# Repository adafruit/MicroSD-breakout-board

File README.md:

## Adafruit MicroSD breakout board PCB
<a href="http://www.adafruit.com/products/254"><br/>
Click here to purchase one from the Adafruit shop</a>

Not just a simple breakout board, this microSD adapter goes the extra mile - designed for ease of use.

- Onboard 5v->3v regulator provides 150mA for power-hungry cards
- 3v level shifting means you can use this with ease on either 3v or 5v systems
- Uses a proper level shifting chip, not resistors: less problems, and faster read/write access
- Use 3 or 4 digital pins to read and write 2Gb+ of storage!
- Activity LED lights up when the SD card is being read or written
- Four #2 mounting holes
- Push-push socket with card slightly over the edge of the PCB so its easy to insert and remove
- Comes with 0.1" header (unattached) so you can get it on a breadboard or use wires - your choice
- Tested and assembled here at the Adafruit factory
- Works great with Arduino, with tons of example code and wiring diagrams

This repo contains the PCB files for the Adafruit SPI Micro SD (transflash) breakout board

### License

Adafruit invests time and resources providing this open source design, please support Adafruit and open-source hardware by purchasing products from [Adafruit](https://www.adafruit.com)!

All text above must be included in any redistribution

Designed by Limor Fried/Ladyada for Adafruit Industries.
Creative Commons Attribution/Share-Alike, all text above must be included in any redistribution. 
See license.txt for additional information.

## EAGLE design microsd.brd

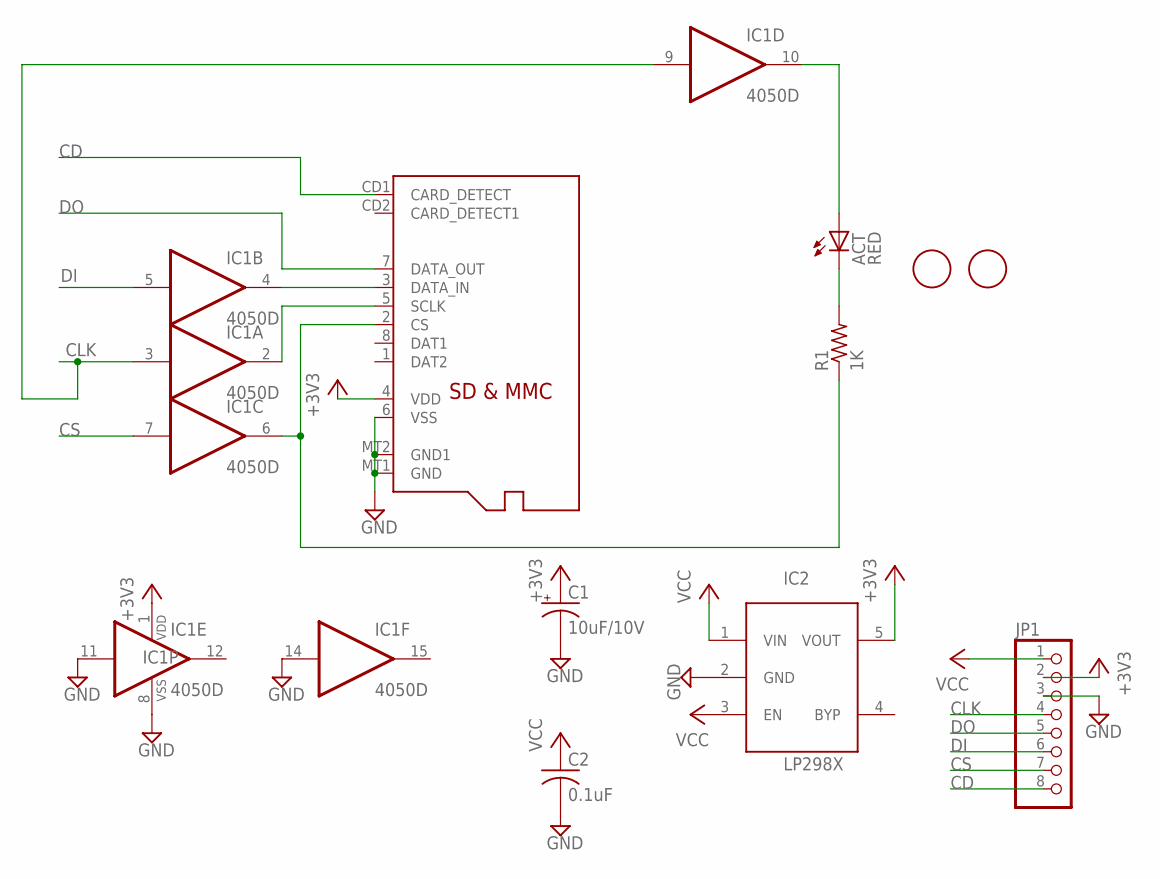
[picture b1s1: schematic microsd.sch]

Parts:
ACT: RED; CHIP-LED0805
C1: 10uF/10V; A/3216-18R
C2: 0.1uF; C0805K
IC1: 4050D; SO16
IC2: LP298XS; SOT23-5L
JP1: PINHD-1X8BIG; 1X08-BIG
R1: 1K; R0805
U$1, U$2: FIDUCIAL; FIDUCIAL_1MM
X1: MICROSD

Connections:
+3V3: C1.+, IC1.1 (VDD), IC2.5 (VOUT), JP1.2, X1.4 (VDD)
CD: JP1.8, X1.CD1 (CARD_DETECT)
CLK: IC1.3 (I), IC1.9 (I), JP1.4
CS: IC1.7 (I), JP1.7
DI: IC1.5 (I), JP1.6
DO: JP1.5, X1.7 (DATA_OUT)
GND: C1.-, C2.2, IC1.8 (VSS), IC1.11 (I), IC1.14 (I), IC2.2 (GND), JP1.3, X1.6 (VSS), X1.MT1 (GND), X1.MT2 (GND1)
unnamed: ACT.A, IC1.10 (O)
unnamed: IC1.2 (O), X1.5 (SCLK)
unnamed: IC1.6 (O), R1.1, X1.2 (CS)
unnamed: ACT.C, R1.2
unnamed: IC1.4 (O), X1.3 (DATA_IN)
VCC: C2.1, IC2.1 (VIN), IC2.3 (EN), JP1.1

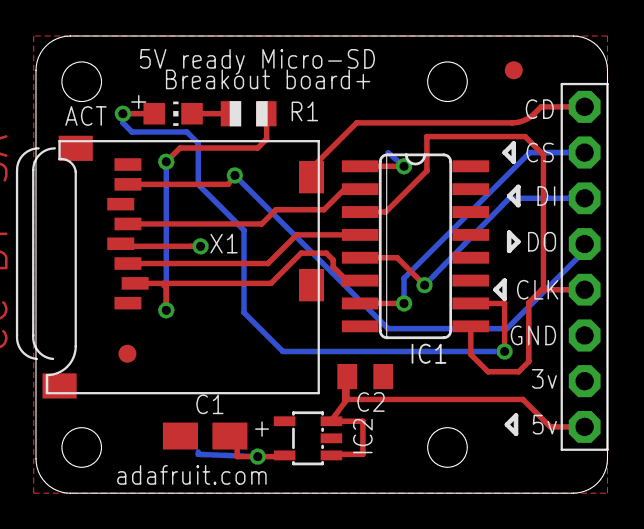
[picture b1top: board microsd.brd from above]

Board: 2 copper layers, 31.8 x 25.4 mm, 10 parts (0 on the bottom side), 13 nets.

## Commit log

2010-07-26 files and schematic image
2011-02-26 tweaks
2014-07-28 re-save as eagle 6

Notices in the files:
microsd.brd:
CC BY-SA
